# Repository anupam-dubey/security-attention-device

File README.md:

# Security attention Timer
</br> 

## Description
USES popular nano mega328P , this device alerts the security person every 15 minutes time by giving alarm if 
person doesn' press the key after 1 minute sms will be transfered to the prerecoreded numbers, best part of this
machine is that it accepts all settings that is day time , night time delay and clock hour minutes using pc.
for which a seperate code is used which gets activated if someone have sended 'y' character on terminal @115200
otherwise it works fine. it have a memory of 3 numbers, if anyone need less then that he can write xxxxxx 10 times to avoid it. It also monitors battery level and show that on LCD along with time remaining.

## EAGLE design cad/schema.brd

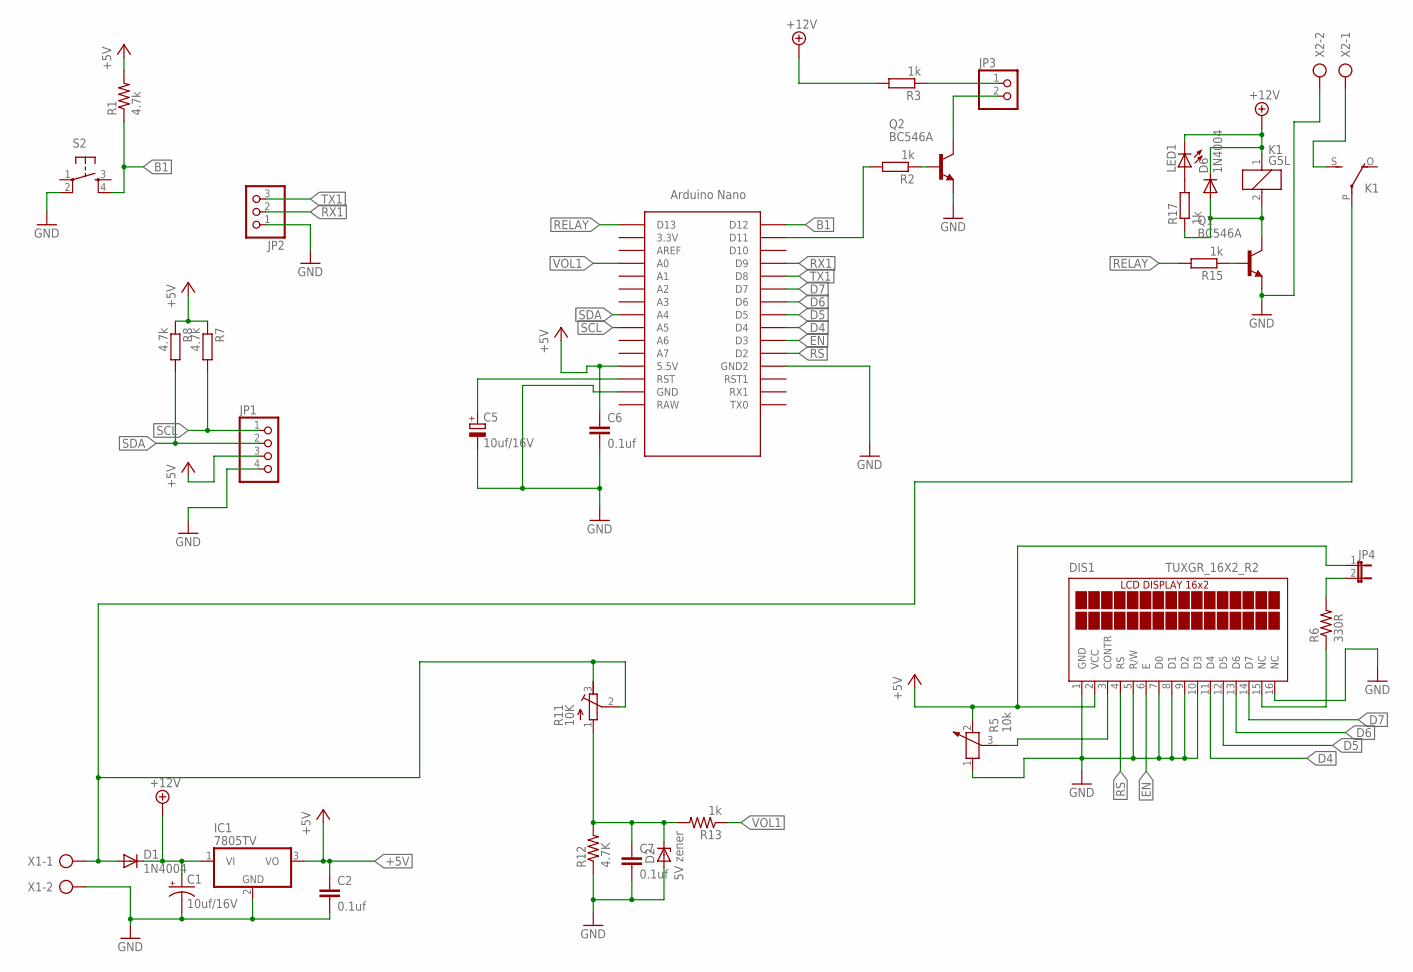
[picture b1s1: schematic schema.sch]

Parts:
C1: 10uf/16V; E2,5-5
C2, C6: 0.1uf; C050-035X075
C5: 10uf/16V; E2-5
C7: 0.1uf; C050-025X075
D1, D6: 1N4004; DO41-10
D2: 1N4728; DO41Z10
DIS1: TUXGR_16X2_R2
IC1: 7805TV; TO220V
JP1: PINHD-1X4; 1X04
JP2: PINHD-1X3; 1X03
JP3: PINHD-1X2; 1X02
JP4: JP1E; JP1
K1: G5L; G5LE
LED1: LED3MM
Q1, Q2: BC546A; TO92-EBC
R1, R7, R8: 4.7k; 0207/10@1
R2, R3, R13, R15: 1k; 0207/10@1
R5: 10k; PT-10
R6: 330R; 0207/10@1
R11: 10K; RTRIM3299W
R12: 4.7K; 0207/10@1
R17: 1k; 0207/5V@1
S2: TAC_SWITCHPTH; TACTILE-PTH
U$1: NANO
X1, X2: AK500/2

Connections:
+5V: C2.1, C6.1, DIS1.2 (VCC), IC1.3 (VO), JP1.3, JP4.1, R1.2, R5.2, R7.1, R8.1, U$1.5V (5.5V)
+12V: C1.+, D1.C, D6.C, IC1.1 (VI), K1.1, LED1.K (C), R3.2
B1: R1.1, S2.4, U$1.D12
D4: DIS1.11 (D4), U$1.D4
D5: DIS1.12 (D5), U$1.D5
D6: DIS1.13 (D6), U$1.D6
D7: DIS1.14 (D7), U$1.D7
EN: DIS1.6 (E), U$1.D3
FEEDER: D1.A, K1.P, R11.2 (S), R11.3 (E), X1.1
GND: C1.-, C2.2, C5.-, C6.2, C7.2, D2.A, DIS1.1 (GND), DIS1.5 (R/W), DIS1.7 (D0), DIS1.8 (D1), DIS1.9 (D2), DIS1.10 (D3), DIS1.16 (NC), IC1.2 (GND), JP1.4, JP2.1, Q1.E, Q2.E, R5.1, R12.1, S2.2, U$1.GND, U$1.GND1 (GND2), X1.2, X2.2
unnamed: JP4.2, R6.2
unnamed: D6.A, K1.2, Q1.C, R17.1
unnamed: K1.S, X2.1
unnamed: C7.1, D2.C, R11.1 (A), R12.2, R13.2
unnamed: C5.+, U$1.RST
unnamed: JP3.2, Q2.C
unnamed: Q2.B, R2.1
unnamed: JP3.1, R3.1
unnamed: DIS1.3 (CONTR), R5.3
unnamed: DIS1.15 (NC), R6.1
unnamed: R2.2, U$1.D11
unnamed: Q1.B, R15.1
unnamed: LED1.A, R17.2
RELAY: R15.2, U$1.D13
RS: DIS1.4 (RS), U$1.D2
RX1: JP2.2, U$1.D9
SCL: JP1.1, R7.2, U$1.A5
SDA: JP1.2, R8.2, U$1.A4
TX1: JP2.3, U$1.D8
VOL1: R13.1, U$1.A0

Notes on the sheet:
5V zener

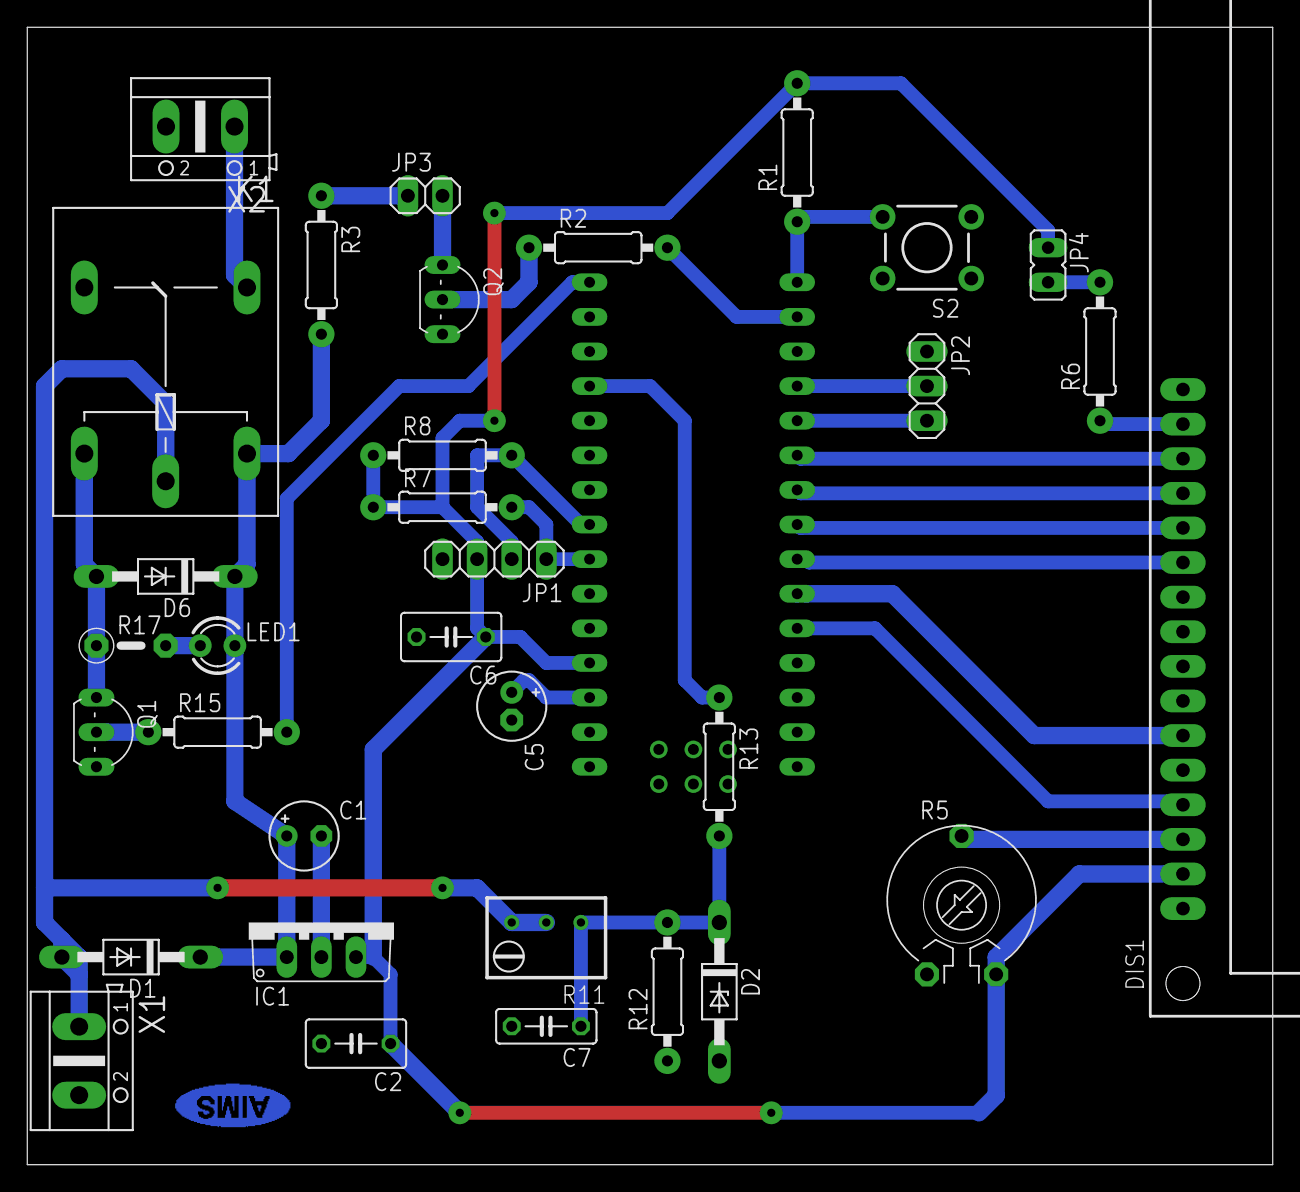
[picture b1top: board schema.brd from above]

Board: 2 copper layers, 91.4 x 83.5 mm, 34 parts (0 on the bottom side), 30 nets.

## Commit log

2021-01-09 second
2021-01-09 third commit
2021-03-02 second commit

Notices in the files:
parts and their libraries:
SparkFun-Retired: Licensing: Creative Commons ShareAlike 4.0 International - https://creativecommons.org/licenses/by-sa/4.0
